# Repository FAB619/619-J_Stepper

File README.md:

<div align="center"><h1 style="font-family: courier;" align="center">619-J_Stepper</h1></div>
<div align="center"></div>
<div align="center"><b>An open source closed loop stepper driver.</b></div>

# 619-J_Stepper
**619-J_Stepper** is an open source micro-controller board used to drive a stepper motor in closed loop mode. The board is generally used on 3D printer steppers or CNC steppers to prevent losing steps. The project is inspired by [**Tropical labs: Mechaduino board**](https://tropical-labs.com/mechaduino/).

Here the **features** of the **619-J_Stepper**:

* **STM32F103C8T6 ARM 32-bit Cortex™-M3** is the CPU of the board. Higher frequency, higher speed and cost-effictive.  

* **Magnetic encoder to Allegro's A1333LLETR-T** Contactless 0° to 360° angle sensor IC ,12bit

* **USB programming** and **serial communication** (serial version)

* High speed printing without losing steps.

* Ported the compilation platform from arduino to PlatformIO —— Convenient for STM32 MCU compilation

* This project support build and upload by platformio, you can use Atom or Code editor (need install platformio) build it or upload firmware.

* Cosed loop motor feedback.

Here are the schematic and the board:

<div align="center"></div>

<div align="center"></div>

<div align="center"></div>

<iframe src="https://myhub.autodesk360.com/ue2824bfc/shares/public/SH919a0QTf3c32634dcfc82b0b883f1f9a82?mode=embed" width="640" height="480" allowfullscreen="true" webkitallowfullscreen="true" mozallowfullscreen="true"  frameborder="0"></iframe>

# Manufacturing

After finishing the Routing and verify the pcb. We made the board at **[JLC PCB](https://jlcpcb.com/)**  and we chose also the PCB Assembly service which was very good.

<div align="center"></div>

Here is the **[BOM needed](https://github.com/FAB619/619-J_Stepper/blob/main/files/BOM_final.xlsx)** for jlcpcb assembly service:

<div align="center"></div>

# Downloads

* [619-J_Stepper schematics](https://github.com/FAB619/619-J_Stepper/tree/main/files/Kicad%20Files)

* [619-J_Stepper board](https://github.com/FAB619/619-J_Stepper/tree/main/files/Kicad%20Files)

* [619-J_Stepper Step](https://github.com/FAB619/619-J_Stepper/blob/main/files/Stepper%20Servo.step)

* [619-J_Stepper BOM](https://github.com/FAB619/619-J_Stepper/blob/main/files/BOM_final.xlsx)

* [619-J_Stepper Position file](https://github.com/FAB619/619-J_Stepper/blob/main/files/Stepper%20Servo-all-pos.csv)

* [619-J_Stepper Gerber](https://github.com/FAB619/619-J_Stepper/tree/main/files/Manufacturing)

# Getting started

To program the board, It is necessary to use an **ST-link v2** Programmer (or a **J-Tag**) using also [ST-link Utility](https://www.st.com/en/development-tools/stsw-link004.html). You can find the **Bin File** we will use to flash the stm32 at this [link](https://github.com/FAB619/619-J_Stepper/tree/main/Bin%20File).

If you don't have an St-link you can use any stm32 board as a programmer as shown in this [link](https://geekilyinteresting.wordpress.com/2014/05/04/using-your-stm32f4-discovery-board-as-a-programmer-and-debugger/)

## Wiring

Use an ST-link to connect to **619-J_Stepper**  

<div align="center"></div>

<div align="center"></div>

<div align="center"></div>

## Connect PC upload firmware
Need to connect STlink's SWDIO,SWCLK,RESET,GND to 619-J_Stepper motherboard's SWDIO,SWCLK,RESET,GND.

If you are using Slink for the first time, you may need to install the driver,Upload firmware by slink.

<div align="center"></div>

<div align="center"></div>

<div align="center"></div>

Connect to your board, you will notice that the sftware recognize your board and shows the memory of the MCU, and the St-link will blink in two diffrent colors.

<div align="center"></div>

 Now you can porceed with loading the **Bin File**

<div align="center"></div>

Upload to your board.

<div align="center"></div>

<div align="center"></div>

**Done**, Program uploaded successfully and an LED will turn on. This means a board programed.

<div align="center"></div>

<div align="center"></div>

# Video

<div align="center"></div>

# License

The hardware is under the Creative Commons Attribution Share-Alike 4.0 License as much of the work is based on Mechaduino project by J. Church.

<br />Ce(tte) œuvre est mise à disposition selon les termes de la <a rel="license" href="http://creativecommons.org/licenses/by-nc-sa/4.0/">Licence Creative Commons Attribution - Pas d’Utilisation Commerciale - Partage dans les Mêmes Conditions 4.0 International</a>.

# Disclaimer

This hardware/software is provided "as is", and you use the hardware/software at your own risk. Under no circumstances shall any author be liable for direct, indirect, special, incidental, or consequential damages resulting from the use, misuse, or inability to use this hardware/software, even if the authors have been advised of the possibility of such damages.

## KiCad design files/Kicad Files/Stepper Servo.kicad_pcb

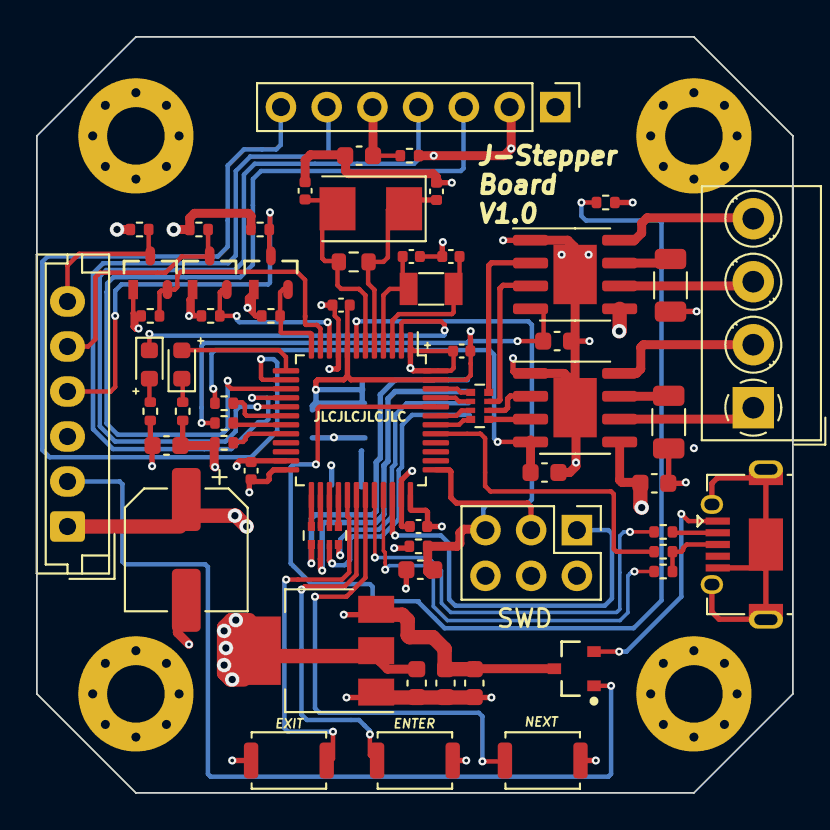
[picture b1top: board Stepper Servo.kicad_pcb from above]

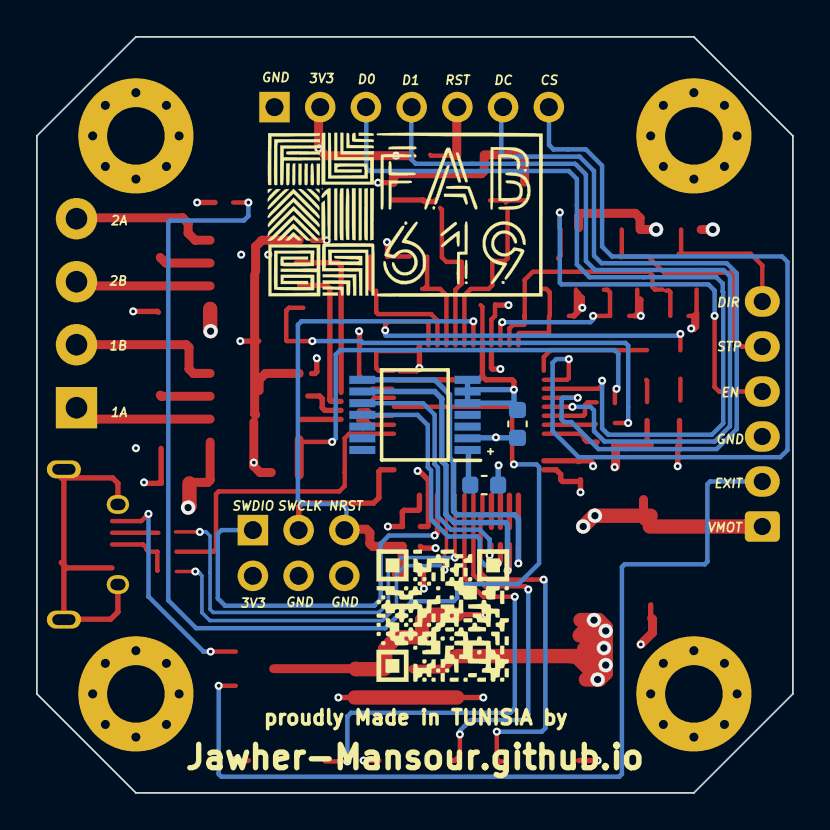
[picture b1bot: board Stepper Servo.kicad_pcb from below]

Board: 4 copper layers, 42.0 x 42.0 mm, 67 parts (3 on the bottom side), 65 nets.

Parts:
C1, C2, C3, C7, C14, C15, C16, C17, C18, C19, C20: 100nF; C_0603_1608Metric
C4, C5: 10pF; C_0402_1005Metric
C6: 100uF; CP_Elec_6.3x5.3
C8, C9: 22pF; C_0402_1005Metric
C10, C11, C12, C13: 100nF; C_0402_1005Metric
D1: LED; LED_0603_1608Metric
D2: LED_Small; LED_0603_1608Metric
D3: BAT64-05; Infineon-BAT64-05-Level_C
H1, H2, H3, H4: MountingHole_Pad; MountingHole_3.2mm_M3_Pad_Via
IC1: A1333LLETR-5-T; SOP65P640X125-14N
J1: USB_B_Micro; USB_Micro-AB_Molex_47590-0001
J2: SWD; PinHeader_2x03_P2.54mm_Vertical
J3: Motor; TerminalBlock_MetzConnect_Type059_RT06304HBWC_1x04_P3.50mm_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
J4: Screen; PinHeader_1x07_P2.54mm_Vertical
J5: Inputs; JST_EH_B6B-EH-A_1x06_P2.50mm_Vertical
Q1, Q2, Q3: FDN337N; ON_Semi-527AG-01-12_2008-O-IPC_C
R1, R3, R10, R12: 1K; R_0402_1005Metric
R2, R11: 0.1; R_1206_3216Metric
R4, R5, R8, R14, R15, R16, R17, R18, R19, R20: 10K; R_0402_1005Metric
R6, R9: 22; R_0402_1005Metric
R7: 1K5; R_0402_1005Metric
R13: 1M; R_0603_1608Metric
RN1: 10; R_Array_Convex_4x0402
RN2: 100; R_Array_Convex_4x0402
SW1, SW2, SW3: SW_DIP_x01; SW_Push_SPST_NO_Alps_SKRK
U1, U3: A4950E; SOIC-8-1EP_3.9x4.9mm_P1.27mm_EP2.41x3.3mm
U2: STM32F103C8T6; LQFP-48_7x7mm_P0.5mm
U4: AMS1117-3.3; SOT-223-3_TabPin2
Y1: 32K768; Crystal_SMD_3215-2Pin_3.2x1.5mm
Y2: 8MHz; Crystal_SMD_5032-2Pin_5.0x3.2mm

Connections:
1A: J3.1, U3.6
1B: J3.2, U3.8
2A: J3.4, U1.8
2B: J3.3, U1.6
+3V3: C10.2, C11.2, C12.2, C13.2, C19.2, C20.2, J2.2, J4.2, Q1.1, Q2.1, Q3.1, R8.1, R10.2, R14.1, R15.1, R17.1, R19.1, U2.1, U2.9, U2.24, U2.36, U2.48, U4.2
+5V: C14.2, C16.2, C18.2, D3.3, IC1.2, U4.3
A2: RN1.8, U2.25
A9450_IN1: RN2.8, U2.42
A9450_IN2: RN2.7, U2.43
A9450_IN3: RN2.6, U2.45
A9450_IN4: RN2.5, U2.46
BOOT0: R5.1, U2.44
BOOT1: R4.1, U2.20
DIR: J5.6, Q3.2, R20.2
DIR1: Q3.3, R19.2, U2.11
EN: J5.4, Q2.2, R18.2
EN1: Q2.3, R17.2, U2.12
ENTER: SW2.1, U2.30
EXIT: SW1.1, U2.29
GND: C1.1, C2.2, C3.1, C4.2, C5.2, C6.2, C7.1, C8.2, C9.2, C10.1, C11.1, C12.1, C13.1, C14.1, C15.1, C16.1, C17.2, C18.1, C19.1, C20.1, H1.1, H2.1, H3.1, H4.1, IC1.5, IC1.6, IC1.7, J1.5, J1.6, J2.4, J2.6, J4.1, J5.3, R2.1, R4.2, R5.2, R11.1, R12.1, SW1.2, SW2.2, SW3.2, U1.1, U1.9, U2.8, U2.23, U2.35, U2.47, U3.1, U3.9, U4.1
IN1: RN2.1, U3.3
IN2: RN2.2, U3.2
IN3: RN2.3, U1.3
IN4: RN2.4, U1.2
MISO: RN1.6, U2.27
MOSI: RN1.5, U2.28
NEXT: SW3.1, U2.31
NRST: C7.2, J2.5, R8.2, U2.7
unnamed: C1.2, R1.1, U1.4
unnamed: C3.2, R3.1, U3.4
unnamed: C15.2, J4.5, R14.2
unnamed: C17.1, IC1.1
unnamed: D1.2, R10.1
unnamed: D2.1, R12.2
unnamed: IC1.8, RN1.1
unnamed: IC1.9, RN1.2
unnamed: IC1.10, RN1.4
unnamed: IC1.11, RN1.3
unnamed: J1.2, R6.1
unnamed: J1.3, R7.2, R9.1
unnamed: R2.2, U1.7
unnamed: R11.2, U3.7
OLED_CS: J4.7, U2.14
OLED_D1: J4.4, U2.17
OLED_DC: J4.6, U2.16
OLED_DO: J4.3, U2.15
OSC32IN: C4.1, U2.3, Y1.1
OSC32OUT: C5.1, U2.4, Y1.2
SCK: RN1.7, U2.26
STP: J5.5, Q1.2, R16.2
STP1: Q1.3, R15.2, U2.10
SWCLK: J2.3, U2.37
SWDIO: J2.1, U2.34
USB_C: R7.1, U2.41
USB_D+: R9.2, U2.33
USB_D-: R6.2, U2.32
VBUS: D3.2, J1.1
VCC: D3.1, J5.2, R16.1, R18.1, R20.1
VMOT: C2.1, C6.1, J5.1, U1.5, U3.5
VREF12: R3.2, U2.18
VREF34: R1.2, U2.19
XTALin: C8.1, R13.1, U2.5, Y2.1
XTALout: C9.1, R13.2, U2.6, Y2.2
bLED: D1.1, U2.2
rLED: D2.2, U2.13

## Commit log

2021-04-22 Upload firmware
2021-04-22 Bin Files
2021-04-22 Update uploading steps
